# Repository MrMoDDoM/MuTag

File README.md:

# MuTag v2.1
Repository for PCB and source file of the MuHack NFC Tag keychain.

This is a custom printed circuit board featuring an ATTiny44a microcontroller and an ST25 NFC ISO15 tag. 

From the MCU is it possible to access the NFC tag using I2C, to modify the tag's configuration and read/write data.

## Features
- ATTiny44a MCU
- ST25 NFC ISO15 tag with 4Kbit memory
- Energy harvesting
- Fast transfer memory, 256bytes of _Mailbox_
- 4 LEDs of different colors
- I2C and UART (TBD) interfaces 
- Small form factor: only 20x60mm

# Getting Started

In the Hardware folder you can find the PCB design files and the schematics. 

```
#define YELLOW_LED 0
#define GREEN_LED 1
#define BLUE_LED 2
#define RED_LED 3
```

The LEDs are connected to:
- Yellow led on pin 0 (Port PA0)
- Green led on pin 1 (Port PA1)
- Blue led on pin 2 (Port PA2)
- Red led on pin 3 (Port PA3)

The NFC tag is connected to the ATTiny's I2C bus:
- SDA on pin 6 (Port PA6)
- SCL on pin 4 (Port PA4)

The NFC GPO is also connected to the ATTiny's INT0 interrupt port (Port PB2).

## Activating Energy Harvesting Mode with the ST25 Android App

By default, the ST25 NFC tag is set to "on demand" energy harvesting mode.
To activate energy harvesting mode on the ST25 NFC IC, you will need to use the ST25 Android app (future implementation of the software will automatically activate this through the I2C communication).

Follow these steps:

1. Download the ST25 Android app from the Google Play Store (https://play.google.com/store/apps/details?id=com.st.st25nfc)

2. Scan the tag with the ST25 Android app and from the left menu go to "Register Management"

3. Re-scan the tag to update the tag's configuration. You will see a register called ``EH_MODE``. By default, this register is set to ``0x01``, which means that energy harvesting mode is set "on demand". To enable energy harvesting mode, change the value of this register to ``0x00``

4. While maintaining the tag in the field, tap the "Save" button to write the new configuration to the tag (the default password is all zeros, just tap "OK" to continue)

## Programming the ATTiny44a MCU

Generally speaking, the ATTiny44a MCU must be programmed using an external ISP programmer. In this case, we will use an Arduino Uno as an ISP programmer (you can use any other Arduino board that can be used as an ISP). 

1. Flash the ```ArduinoISP``` sketch (found in the File -> Example menu) to an Arduino (or any other Arduino board that can be used as an ISP)

2. Add the following line to "Additional Boards Manager URLs" in the Arduino IDE preferences:

```http://drazzy.com/package_drazzy.com_index.json```

3. Install the ```ATTinyCore``` by __Spence Konde__ board definition (found in the Tool -> Board -> Board Manager menu) and select the following settings:

| Setting | Value |
|---------|-------|
| Board | ATTiny24/44/84 (noBootloader) |
| Chip | ATTiny44(a) (*Note: for v2.0 select 24*)|
| Clock | 1 MHz internal |
| BOD | Disabled |
| LTO | Enabled |
| EEPROM | EEPROM retained |
| millis()/micros() | Enabled |
| Programmer | Arduino as ISP |

4. Connect the MuTag to the Arduino as follows:

| MuTag | Arduino |
|-------|---------|
| VDD   | 5V      |
| GND   | GND     |
| SCK   | 13      |
| MISO  | 12      |
| MOSI  | 11      |
| RST   | 10      |

~~*NOTE: The MuTag through hole ports are of 1.27mm diameter, enough to fit a common jumper wire. So with a little bit of patience you can push the pin rigth into the hole without soldering.*~~ 

*The holes dimension was changed to a standard 2.54mm in the v2.1*

5. Take another jump wire and connect it the ```RESET``` pin of the Arduino and leave the other end unconnected

6. Now the tricky part: to program the MuTag we need to send the Arduino in "reset mode" for a short period of time. To do this, we need to connect the ```RESET``` pin of the Arduino to ground (i.e. by touching the USB ground shield with the unconnected end the ```RESET``` wire) rigth before we press the "Upload" button in the Arduino IDE. Wait about 2/3 seconds and then release the RESET wire. You should see the Arduino IDE uploading the sketch to the MuTag.

*NOTE: Depending on your Arduino IDE version, you might need to use the "Upload using Programmer" option in the Sketch menu instead of the "Upload" button.*

## Accessing the NFC Tag with the I2C Interface
The internal memory of the ST25 NFC tag can be accessed through the I2C bus as a standard EEPROM memory. The I2C address of the tag is ```0x53```.

The "Hello_MuHack.ino" sketch is a simple example of how to read and write data to the tag.

## TODOS:
- [ ] Add a 3D model of the PCB
- [ ] Find a good bootloader to enable UART programming 
- [x] Evaluate the possibility of removing the diodes
- [x] Evaluate to move and make bigger pads for programming
- [x] Evaluate to change the MCU to an ATTiny44/84 to have more memory
- [x] Evaluate to remove the ```RESET``` pad

## Notes on the Bootloader
The bootloader is a small piece of code that is stored in the MCU's memory and that allows to program via UART. This is very useful because it avoid the need of an external SPI programmer.

The [Optiboot version compiled by Spence Konde](https://github.com/SpenceKonde/ATTinyCore/blob/v2.0.0-devThis-is-the-head-submit-PRs-against-this/avr/extras/ATtiny_x4.md#optiboot-bootloader) uses the pins ```AIN0``` and ```AIN1```, currently connected to the LEDs. This leaves us with two options:
- Remove the LEDs and use the pins for programming via UART
- Recompiling the bootloader to use different pins

Since this project is intended to be used as a keychain, which means that is to be programmed only once, I decided to not invest time in the bootloader and leave the LEDs as they are.

## License
Copyright (c) 2023 MrMoDDoM

This project is licensed under the GNU AFFERO GENERAL PUBLIC License - see the [LICENSE.md](LICENSE.md) file for details

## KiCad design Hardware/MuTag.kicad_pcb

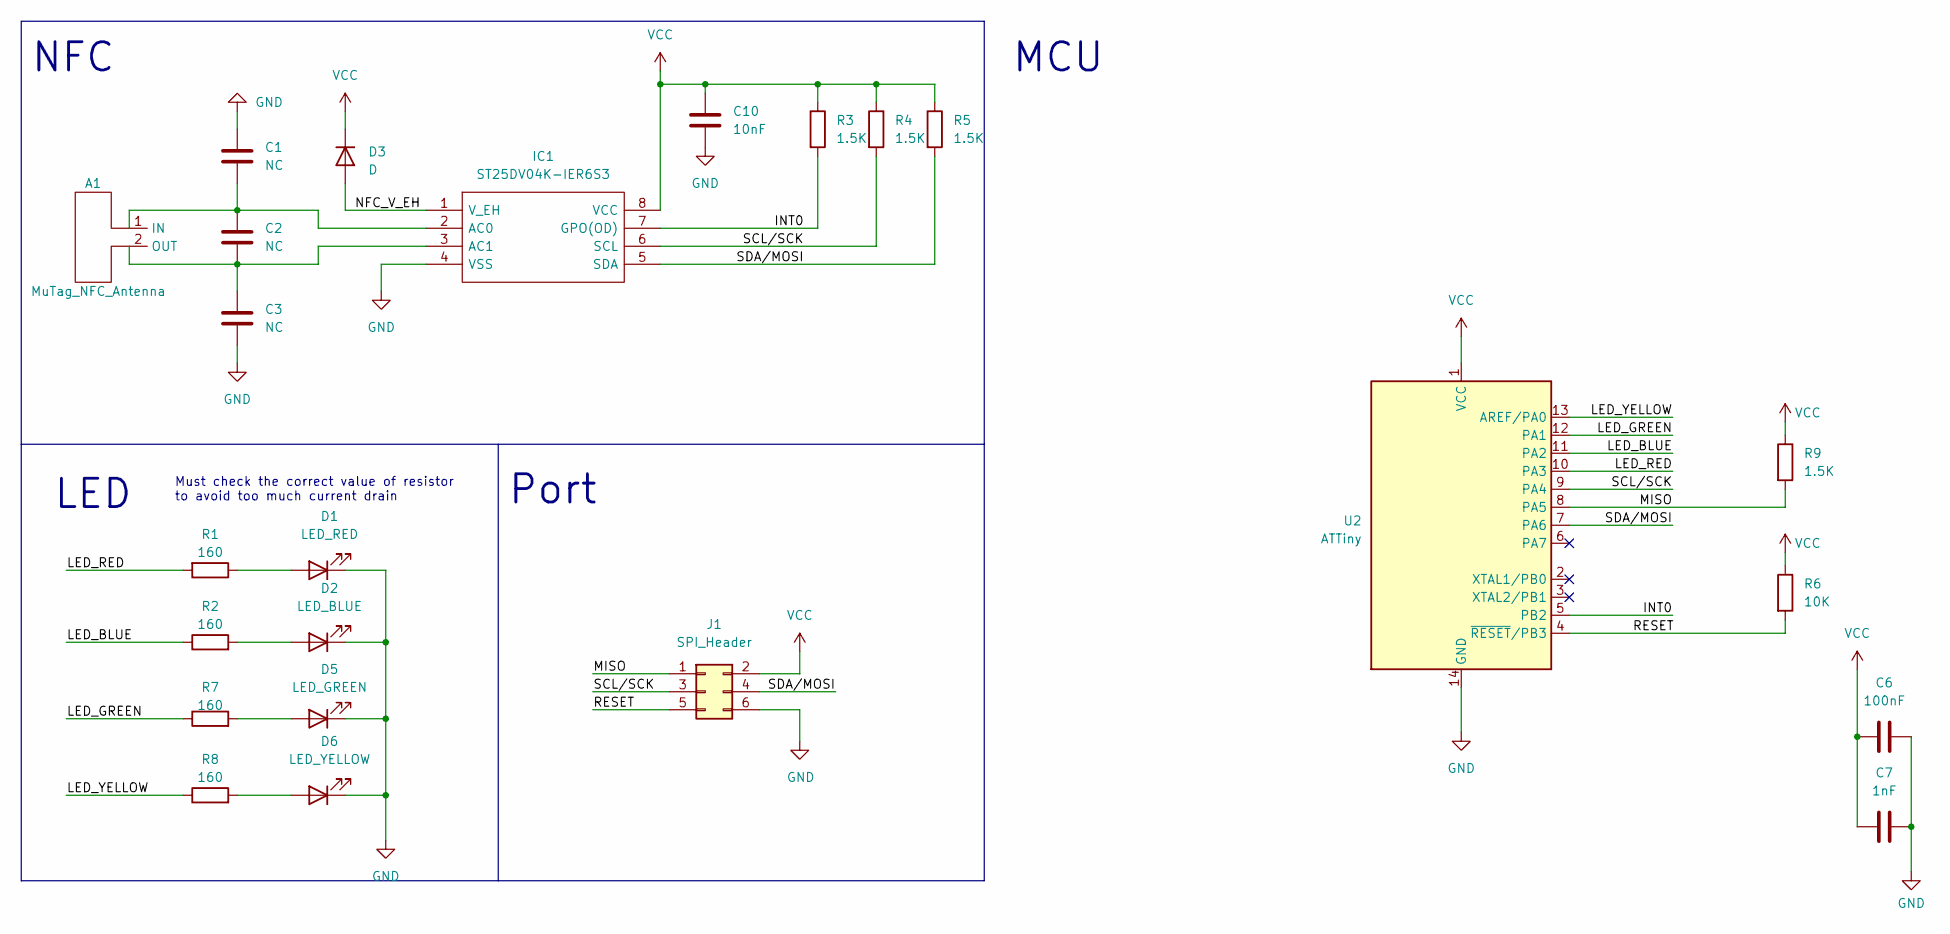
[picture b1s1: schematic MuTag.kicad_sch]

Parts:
A1: MuTag_NFC_Antenna; mutag_new_antenna
C1, C2, C3: NC; C_0402_1005Metric
C6: 100nF; C_0402_1005Metric
C7: 1nF; C_0402_1005Metric
C10: 10nF; C_0402_1005Metric
D1: LED_RED; LED_0603_1608Metric
D2: LED_BLUE; LED_0603_1608Metric
D3: D; D_SOD-123F
D5: LED_GREEN; LED_0603_1608Metric
D6: LED_YELLOW; LED_0603_1608Metric
IC1: ST25DV04K-IER6S3; SOIC127P600X175-8N; Manufacturer_Part_Number ST25DV04K-IER6S3; Mouser Part Number 511-ST25DV04K-IER6S3
J1: SPI_Header; PinHeader_2x03_P2.54mm_Vertical
R1, R2, R7, R8: 160; R_0402_1005Metric
R3, R4, R5, R9: 1.5K; R_0402_1005Metric
R6: 10K; R_0402_1005Metric
U2: ATTiny; SOIC-14_3.9x8.7mm_P1.27mm

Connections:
/INT0: IC1.7 (GPO(OD)), R3.2, U2.5 (PB2)
/LED_BLUE: R2.1, U2.11 (PA2)
/LED_GREEN: R7.1, U2.12 (PA1)
/LED_RED: R1.2, U2.10 (PA3)
/LED_YELLOW: R8.1, U2.13 (AREF/PA0)
/MISO: J1.1, R9.2, U2.8 (PA5)
/NFC_V_EH: D3.2 (A), IC1.1 (V_EH)
/RESET: J1.5, R6.2, U2.4 (~RESET/PB3)
/SCL/SCK: IC1.6 (SCL), J1.3, R4.2, U2.9 (PA4)
/SDA/MOSI: IC1.5 (SDA), J1.4, R5.2, U2.7 (PA6)
GND: C1.1, C3.2, C6.2, C7.2, C10.2, D1.1 (K), D2.1 (K), D5.1 (K), D6.1 (K), IC1.4 (VSS), J1.6, U2.14 (GND)
unnamed: A1.1 (IN), C1.2, C2.1, IC1.2 (AC0)
unnamed: A1.2 (OUT), C2.2, C3.1, IC1.3 (AC1)
unnamed: D1.2 (A), R1.1
unnamed: D2.2 (A), R2.2
unnamed: D5.2 (A), R7.2
unnamed: D6.2 (A), R8.2
VCC: C6.1, C7.1, C10.1, D3.1 (K), IC1.8 (VCC), J1.2, R3.1, R4.1, R5.1, R6.1, R9.1, U2.1 (VCC)

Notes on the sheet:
NFC
LED
Port
Must check the correct value of resistor to avoid too much current drain
MCU

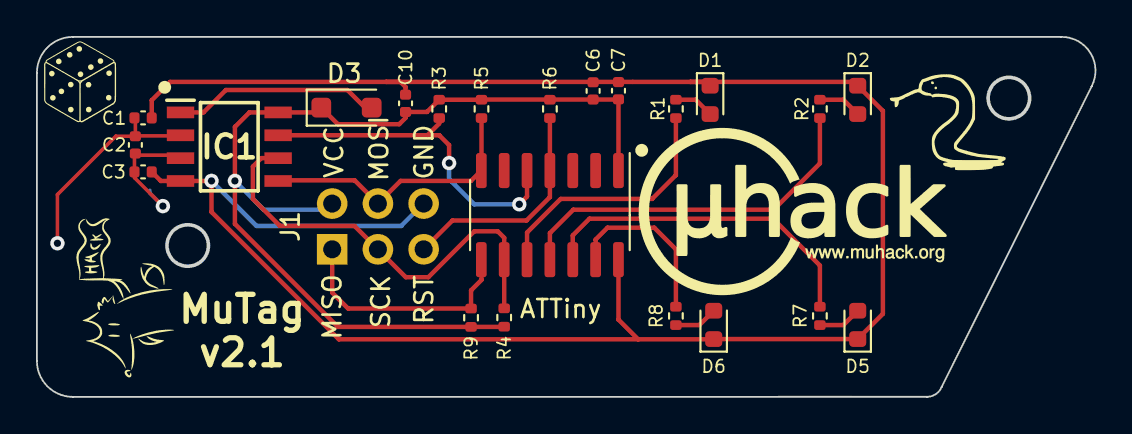
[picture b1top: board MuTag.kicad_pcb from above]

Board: 2 copper layers, 58.8 x 20.0 mm, 24 parts (1 on the bottom side), 18 nets.

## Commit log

2023-01-23 First commit - hardware only. Modified gitignore
2023-02-12 Updated the readme - added blink source and image
2023-03-08 First routing of new version - no antenna
2023-03-09 New finished routing, with bigger antenna and leds - ready for production
2023-03-25 Ordered Version v2
2023-04-08 Second version first commit - produced and tested: all working
2023-04-13 Version v2.1 - Set production and docs with ATTiny44a, removed diode from VCC port, moved components to fit bigger port, led resistors value changed to 160
2023-04-19 Modified led resistor to 150 - increased distance between components to be hand soldered - modified graphics
2023-05-22 Updated the readme - need to update the photo
2023-05-27 Updated image and bug-fixed README
